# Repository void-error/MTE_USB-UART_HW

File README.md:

# MTE_USB-UART_HW
USB interface for MTE projects

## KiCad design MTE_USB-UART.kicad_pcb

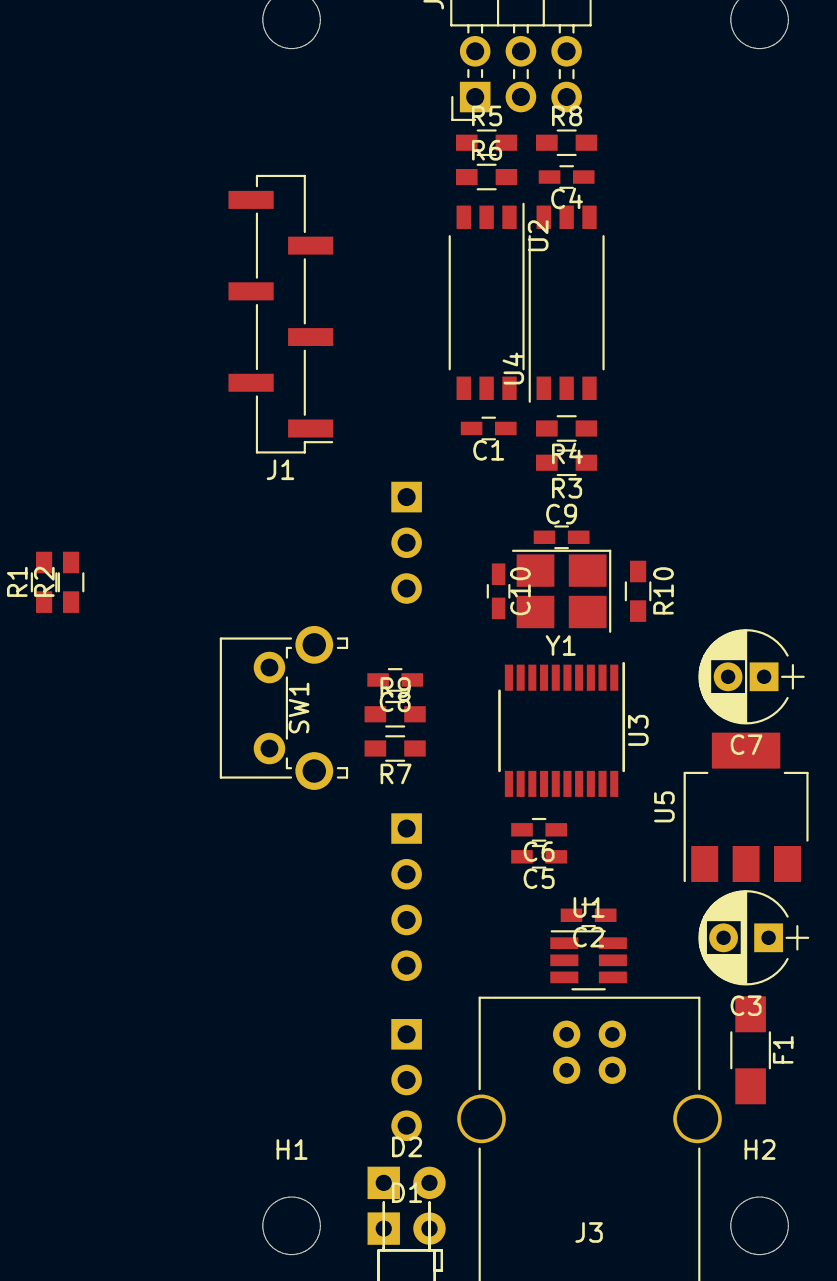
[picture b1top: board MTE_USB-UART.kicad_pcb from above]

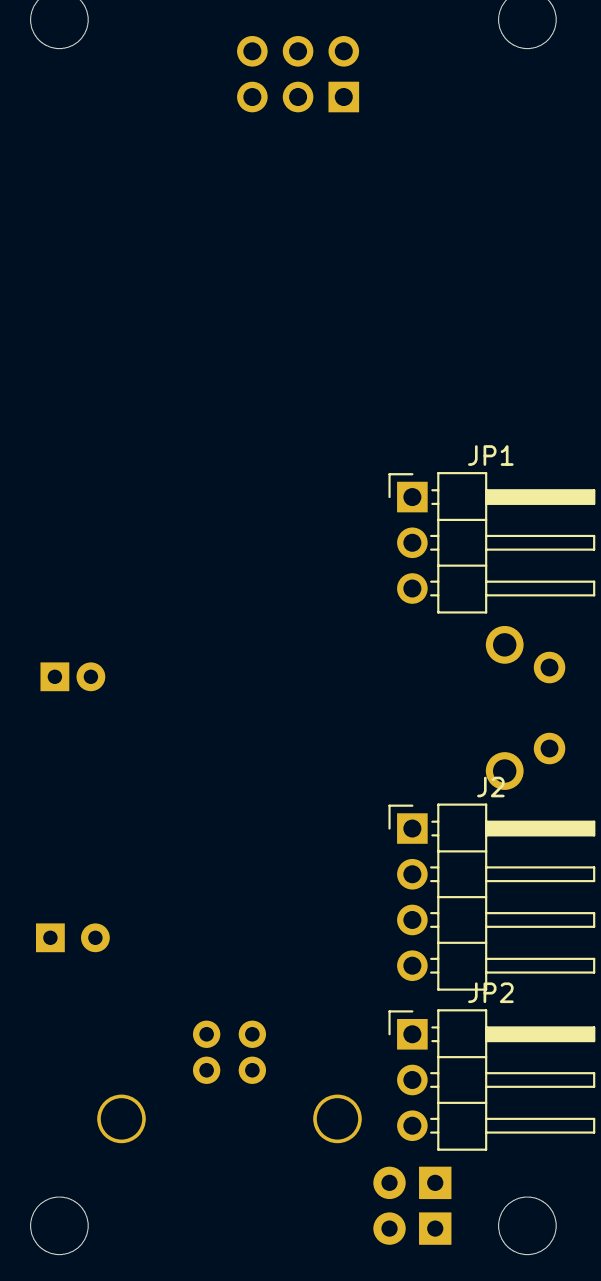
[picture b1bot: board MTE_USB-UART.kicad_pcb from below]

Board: 2 copper layers, 40 parts (3 on the bottom side), 31 nets, no tracks yet.

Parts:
C1, C4: C; C_0603_HandSoldering
C2, C6, C8: 100n; C_0603_HandSoldering
C3: 10u; CP_Radial_D5.0mm_P2.50mm
C5: 4u7; C_0603_HandSoldering
C7: 10u; CP_Radial_D5.0mm_P2.00mm
C9, C10: 18p; C_0603_HandSoldering
D1: LED; LED_D3.0mm_Horizontal_O1.27mm_Z2.0mm
D2: LED; LED_D3.0mm_Horizontal_O3.81mm_Z6.0mm
F1: Polyfuse; R_1206_HandSoldering
H1, H2, H3, H4: MountingHole; MountingHole_3.2mm_M3
J1: Conn_01x06; Pin_Header_Straight_1x06_Pitch2.54mm_SMD_Pin1Left
J2: Conn_01x04; Pin_Header_Angled_1x04_Pitch2.54mm
J3: USB_B
J4: Conn_02x03_Odd_Even; Pin_Header_Angled_2x03_Pitch2.54mm
JP1, JP2: Jumper_3_Bridged12; Pin_Header_Angled_1x03_Pitch2.54mm
R1, R2: 1k; R_0603_HandSoldering
R3, R4, R5, R6: 3k3; R_0603_HandSoldering
R7, R10: 10k; R_0603_HandSoldering
R8, R9: 100R; R_0603_HandSoldering
SW1: SW_Push; SW_Tactile_SPST_Angled_PTS645Vx31-2LFS
U1: USBLC6-2SC6; SOT-23-6_Handsoldering
U2, U4: TLP2761; SO-6L_10x3.84mm_Pitch1.27mm
U3: STM32F070F6Px; TSSOP-20_4.4x6.5mm_Pitch0.65mm
U5: NCP1117-3.3_SOT223; SOT-223-3_TabPin2
Y1: 8MHz; Crystal_SMD_3225-4pin_3.2x2.5mm_HandSoldering

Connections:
+3V3D: C1.1, C5.1, C6.1, C7.1, J2.1, JP1.1, JP2.1, JP2.2, R3.1, R7.2, U2.6, U3.5, U3.16, U5.2
+3V3I: C4.2, J4.1, R5.1, U4.6
/SWCLK: J2.3, U3.20
/SWDIO: J2.2, U3.19
/USB_DM: U1.4, U3.17
/USB_DP: U1.6, U3.18
DGND: C1.2, C2.2, C3.2, C5.2, C6.2, C7.2, C8.2, C9.1, C10.1, D1.1, D2.1, J1.6, J2.4, J3.4, J3.5, R4.1, R10.1, SW1.2, U1.2, U2.4, U3.15, U5.1, Y1.2, Y1.4
IGND: C4.1, J4.2, J4.4, J4.6, R6.1, U4.4
unnamed: C8.1, R7.1, R9.2, U3.4
unnamed: C9.2, U3.2, Y1.1
unnamed: C10.2, U3.3, Y1.3
unnamed: D1.2, R1.1
unnamed: D2.2, R2.1
unnamed: F1.2, J3.1
unnamed: J1.1, JP1.2
unnamed: J1.2, U3.6
unnamed: J1.3, U3.7
unnamed: J1.4, U3.8, U4.3
unnamed: J1.5, U2.5, U3.9
unnamed: J3.2, U1.3
unnamed: J3.3, U1.1
unnamed: J4.3, U2.3
unnamed: J4.5, R8.1
unnamed: JP2.3, R10.2, U3.1
unnamed: R1.2, U3.10
unnamed: R2.2, U3.11
unnamed: R3.2, R4.2, U4.1
unnamed: R5.2, R6.2, U2.1
unnamed: R8.2, U4.5
unnamed: R9.1, SW1.1
VBUS: C2.1, C3.1, F1.1, JP1.3, U1.5, U5.3

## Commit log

2019-04-12 Work in progress...
